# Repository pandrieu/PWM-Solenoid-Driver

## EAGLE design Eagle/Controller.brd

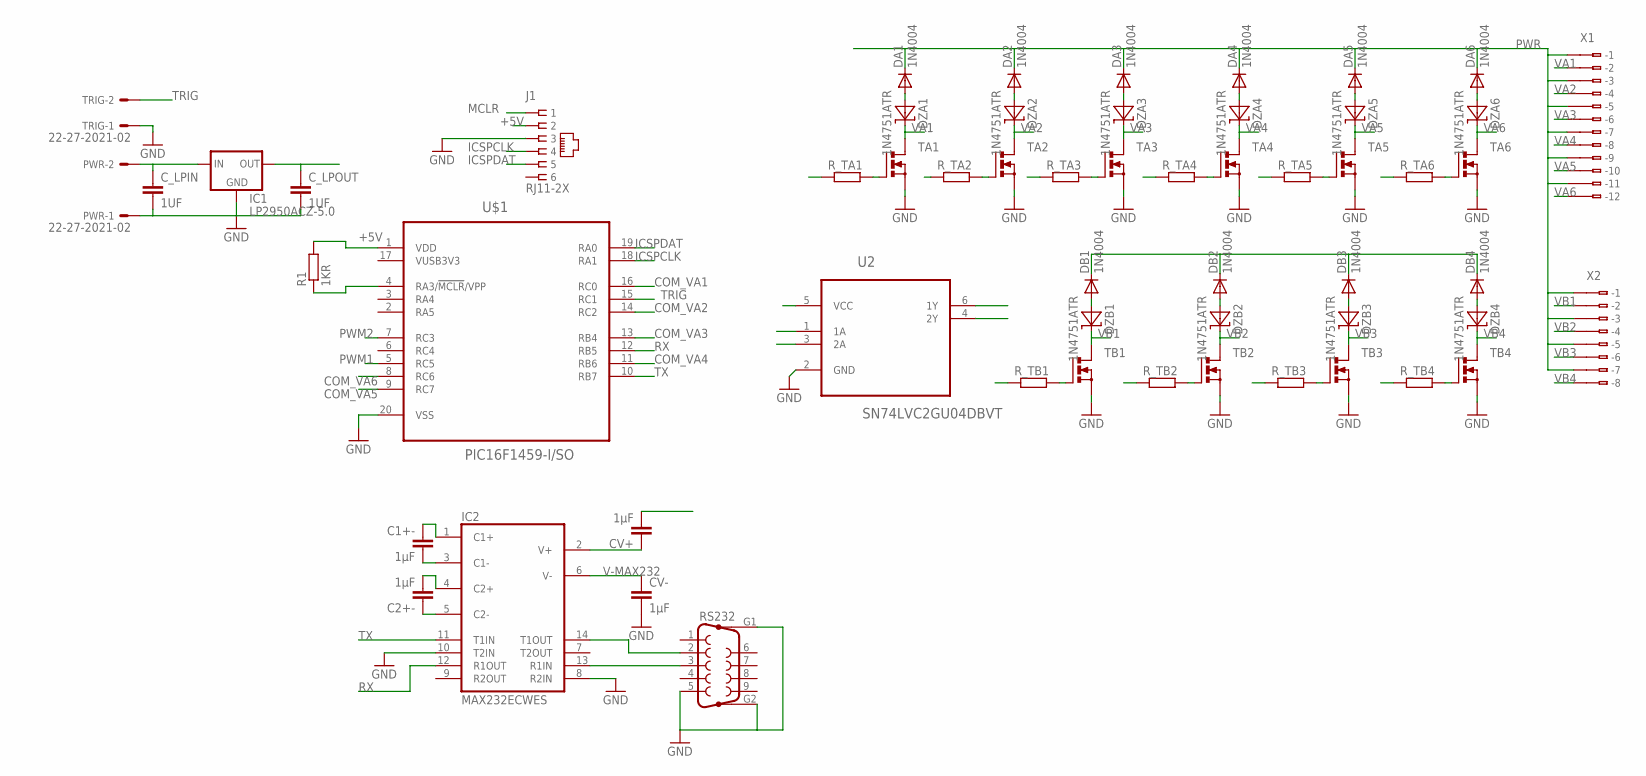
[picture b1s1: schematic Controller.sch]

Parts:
C1+-, C2+-: 1µF; C0805
CV+: 1µF; C0805
CV-: 1µF; C0805
C_LPIN: 1UF; C0805
C_LPOUT: 1UF; C0805
DA1, DA2, DA3, DA4, DA5, DA6: 1N4004; DO41-10
DB1, DB2, DB3, DB4: 1N4004; DO41-10
DZA1, DZA2, DZA3, DZA4, DZA5, DZA6: 1N4751ATR; DO41-7
DZB1, DZB2, DZB3, DZB4: 1N4751ATR; DO41-7
IC1: LP2950ACZ-5.0; TO92
IC2: MAX232ECWES; SO16
J1: RJ11-2X; RJ11-NO_SHIELD
PWR: 22-27-2021-02; 6410-02
R1: 1KR; R0805
RS232: F09HP
R_TA1, R_TA2, R_TA3, R_TA4, R_TA5, R_TA6: R-EU_R0805; R0805
R_TB1, R_TB2, R_TB3, R_TB4: R-EU_R0805; R0805
TA1, TA2, TA3, TA4, TA5, TA6: BSS316N; INF-PG-SOT23_N_1PRIMARY
TB1, TB2, TB3, TB4: BSS316N; INF-PG-SOT23_N_1PRIMARY
TRIG: 22-27-2021-02; 6410-02
U2: SN74LVC2GU04DBVT; SOT95P280X145-6N
U$1: PIC16F1459-I/SO; SOIC127P1030X265-20N
X1: 233-212
X2: 233-208

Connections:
+5V: CV+.2, C_LPOUT.1, IC1.1 (OUT), J1.2, R1.2, U2.5 (VCC), U$1.1 (VDD)
COM_VA1: R_TA1.1, U$1.16 (RC0)
COM_VA2: R_TA2.1, U$1.14 (RC2)
COM_VA3: R_TA3.1, U$1.13 (RB4)
COM_VA4: R_TA4.1, U$1.11 (RB6)
COM_VA5: R_TA5.1, U$1.9 (RC7)
COM_VA6: R_TA6.1, U$1.8 (RC6)
GND: CV-.2, C_LPIN.2, C_LPOUT.2, IC1.2 (GND), IC2.8 (R2IN), IC2.10 (T2IN), IC2.15 (GND), J1.3, PWR.1, RS232.5, RS232.G1, RS232.G2, TA1.2 (S), TA2.2 (S), TA3.2 (S), TA4.2 (S), TA5.2 (S), TA6.2 (S), TB1.2 (S), TB2.2 (S), TB3.2 (S), TB4.2 (S), TRIG.1, U2.2 (GND), U$1.20 (VSS)
ICSPCLK: J1.4, U$1.18 (RA1)
ICSPDAT: J1.5, U$1.19 (RA0)
MCLR: J1.1, R1.1, U$1.4 (RA3/!MCLR!/VPP)
unnamed: DA1.A, DZA1.A
unnamed: DA2.A, DZA2.A
unnamed: C1+-.1, IC2.1 (C1+)
unnamed: DA3.A, DZA3.A
unnamed: C2+-.2, IC2.4 (C2+)
unnamed: DA4.A, DZA4.A
unnamed: IC2.14 (T1OUT), RS232.2
unnamed: IC2.13 (R1IN), RS232.3
unnamed: DA5.A, DZA5.A
unnamed: DA6.A, DZA6.A
unnamed: R_TA1.2, TA1.1 (G)
unnamed: R_TA2.2, TA2.1 (G)
unnamed: R_TA3.2, TA3.1 (G)
unnamed: R_TA4.2, TA4.1 (G)
unnamed: R_TA5.2, TA5.1 (G)
unnamed: R_TA6.2, TA6.1 (G)
unnamed: DB1.A, DZB1.A
unnamed: R_TB1.2, TB1.1 (G)
unnamed: DB2.A, DZB2.A
unnamed: R_TB2.2, TB2.1 (G)
unnamed: DB3.A, DZB3.A
unnamed: C1+-.2, IC2.3 (C1-)
unnamed: R_TB3.2, TB3.1 (G)
unnamed: DB4.A, DZB4.A
unnamed: R_TB4.2, TB4.1 (G)
unnamed: C2+-.1, IC2.5 (C2-)
unnamed: CV+.1, IC2.2 (V+)
PWM1: R_TB1.1, U2.1 (1A), U$1.5 (RC5)
PWM1_INV: R_TB3.1, U2.6 (1Y)
PWM2: R_TB2.1, U2.3 (2A), U$1.7 (RC3)
PWM2_INV: R_TB4.1, U2.4 (2Y)
PWR: C_LPIN.1, DA1.C, DA2.C, DA3.C, DA4.C, DA5.C, DA6.C, IC1.3 (IN), PWR.2, X1.B1 (B-1), X1.B3 (B-3), X1.B5 (B-5), X1.B7 (B-7), X1.B9 (B-9), X1.B11 (B-11), X2.B1 (B-1), X2.B3 (B-3), X2.B5 (B-5), X2.B7 (B-7)
PWR1: DB1.C, DB2.C, DB3.C, DB4.C
RX: IC2.12 (R1OUT), U$1.12 (RB5)
TRIG: TRIG.2, U$1.15 (RC1)
TX: IC2.11 (T1IN), U$1.10 (RB7)
V-MAX232: CV-.1, IC2.6 (V-)
VA1: DZA1.C, TA1.3 (D), X1.B2 (B-2)
VA2: DZA2.C, TA2.3 (D), X1.B4 (B-4)
VA3: DZA3.C, TA3.3 (D), X1.B6 (B-6)
VA4: DZA4.C, TA4.3 (D), X1.B8 (B-8)
VA5: DZA5.C, TA5.3 (D), X1.B10 (B-10)
VA6: DZA6.C, TA6.3 (D), X1.B12 (B-12)
VB1: DZB1.C, TB1.3 (D), X2.B2 (B-2)
VB2: DZB2.C, TB2.3 (D), X2.B4 (B-4)
VB3: DZB3.C, TB3.3 (D), X2.B6 (B-6)
VB4: DZB4.C, TB4.3 (D), X2.B8 (B-8)
VCC: IC2.16 (VCC)
VUSB3V3: U$1.17 (VUSB3V3)

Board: 2 copper layers, 57 parts (0 on the bottom side), 58 nets, no tracks yet.

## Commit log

2016-05-27 new rules for ealge files in gitignore
2016-05-27 Creation of eagle schematic : can be modified during the board routing.
2016-05-27 Creation of the eagle schematic : can be modified during the board routing.
